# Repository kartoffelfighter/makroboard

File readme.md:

# Makroboard 

This keyboard has 8 cherry switches and 8 rgb-leds, connected to an ATMEGA32U4 (Arduino Leonardo) to emulate a keyboard.

Its porpuse is to store Makros which are not defined per default on a keyboard

## Keys

Default layout (in firmware folder)

| CTRL + F1  | CTRL + F2   | CTRL + F3  | CTRL + F4  |
| ---------- | ----------- | ---------- | ---------- |
| Media_PREV | Media_PAUSE | Media_NEXT | Media_STOP |
|            |             |            |            |
## Dependencies

The firmware uses the FastLed and Project-HID Librarys. You can find these on github, but also in the arduino library manager.

[FastLed (FastLED)]: https://github.com/FastLED/FastLED
[Project-HID (NicoHood)]: https://github.com/NicoHood/HID

### Notes

The Source code is not optimized and might hang sometimes. Since i'm using this board at most to control my teamspeak-mute i didn't care to optimize. If you wan't to, feel free.

Software and Hardware come as-is without any warranty.

My board was etched at jlcpcb, parts came from mouser, assembling was done by hand. 

If you're interested in a board feel free to contact me, i do still have some laying here.

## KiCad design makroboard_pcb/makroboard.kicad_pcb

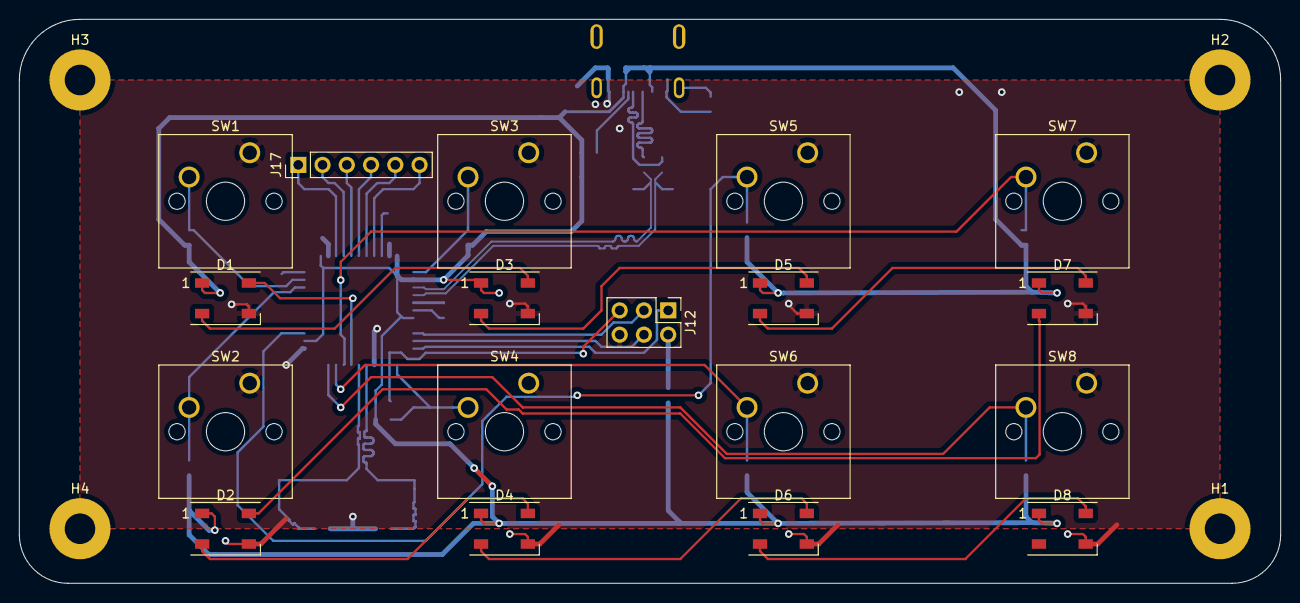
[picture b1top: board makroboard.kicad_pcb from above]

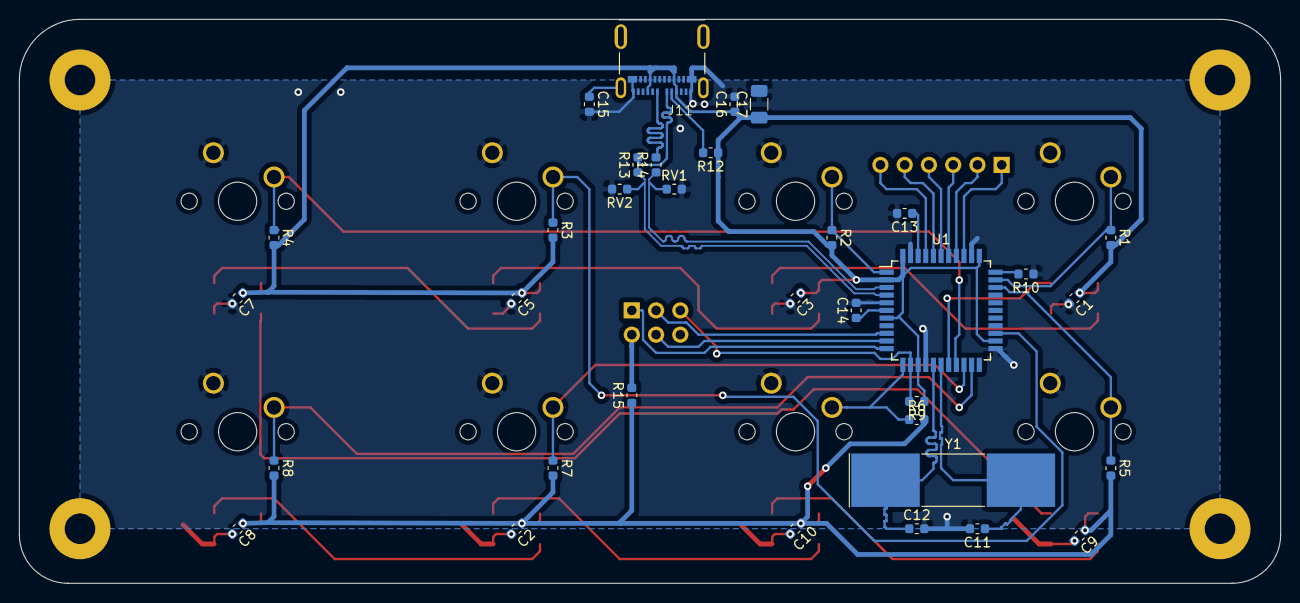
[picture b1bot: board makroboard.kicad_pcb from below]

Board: 2 copper layers, 132.1 x 59.1 mm, 56 parts (34 on the bottom side), 40 nets.

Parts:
C1, C2, C3, C5, C7, C8, C9, C10, C13: 100n; C_0603_1608Metric
C11, C12: 22pF; C_0603_1608Metric
C14: 1µ; C_0603_1608Metric
C15: 1nF; C_0603_1608Metric
C16: 100nF; C_0603_1608Metric
C17: 1µF; C_1206_3216Metric
D1, D2, D3, D4, D5, D6, D7, D8: WS2812B; LED_WS2812B_PLCC4_5.0x5.0mm_P3.2mm
H1, H2, H3, H4: MountingHole_Pad; MountingHole_3.2mm_M3_Pad
J11: 105450-0101; MOLEX_105450-0101
J12: ICSP; PinHeader_2x03_P2.54mm_Vertical
J17: ANALOG_IO; PinHeader_1x06_P2.54mm_Vertical
R1, R2, R3, R4, R5, R6, R7, R8, R9, R10: 10k; R_0603_1608Metric
R12: 56k; R_0603_1608Metric
R13, R14: 22R; R_0603_1608Metric
R15: 0R0; R_0603_1608Metric
RV1, RV2: Varistor; R_0603_1608Metric
SW1, SW2, SW3, SW4, SW5, SW6, SW7, SW8: SW_Push; SW_Cherry_MX_1.50u_PCB
U1: ATmega32U4-AU; TQFP-44_10x10mm_P0.8mm
Y1: 16MHz; Crystal_SMD_SeikoEpson_MA505-2Pin_12.7x5.1mm_HandSoldering

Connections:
+5V: C1.1, C2.1, C3.1, C5.1, C7.1, C8.1, C9.1, C10.1, C16.1, C17.1, D1.1, D2.1, D3.1, D4.1, D5.1, D6.1, D7.1, D8.1, J11.A4, J11.A9, J11.B4, J11.B9, R1.2, R2.2, R3.2, R4.2, R5.2, R6.2, R7.2, R8.2, R9.1, R12.1, R15.1, U1.2, U1.7, U1.14, U1.24, U1.34, U1.44
A0: J17.1, U1.36
A1: J17.2, U1.37
A2: J17.3, U1.38
A3: J17.4, U1.39
A4: J17.5, U1.40
A5: J17.6, U1.41
D0: R7.1, SW6.2, U1.20
D1: R8.1, SW8.2, U1.21
D2: R4.1, SW7.2, U1.19
D3: D1.4, U1.18
D4: R3.1, SW5.2, U1.25
D5: R5.1, SW2.2, U1.31
D7: R2.1, SW3.2, U1.1
D11: R6.1, SW4.2, U1.12
D13: R1.1, SW1.2, U1.32
GND: C1.2, C2.2, C3.2, C5.2, C7.2, C8.2, C9.2, C10.2, C11.2, C12.2, C13.2, C14.2, C15.2, C16.2, C17.2, D1.3, D2.3, D3.3, D4.3, D5.3, D6.3, D7.3, D8.3, J11.A1, J11.A12, J11.B1, J11.B12, J12.6, R10.1, RV1.2, RV2.2, SW1.1, SW2.1, SW3.1, SW4.1, SW5.1, SW6.1, SW7.1, SW8.1, U1.5, U1.15, U1.23, U1.35, U1.43
MISO: J12.1, U1.11
MOSI: J12.4, U1.10
unnamed: C11.1, U1.17, Y1.2
unnamed: C12.1, U1.16, Y1.1
unnamed: C13.1, U1.42
unnamed: C14.1, U1.6
unnamed: C15.1, J11.S1, J11.S2, J11.S3, J11.S4
unnamed: D1.2, D3.4
unnamed: D2.2, D4.4
unnamed: D2.4, D7.2
unnamed: D3.2, D5.4
unnamed: D4.2, D6.4
unnamed: D5.2, D7.4
unnamed: D6.2, D8.4
unnamed: J11.A5, R12.2
unnamed: J11.A6, R13.2
unnamed: J11.A7, R14.2
unnamed: J12.2, R15.2
unnamed: R10.2, U1.33
RESET: J12.5, R9.2, U1.13
SCK: J12.3, U1.9
USB_D+: R13.1, RV2.1, U1.4
USB_D-: R14.1, RV1.1, U1.3

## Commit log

2020-05-24 add: stls for case & current bom
2020-08-16 LICENSE hinzufügen
2020-12-26 working firmware with 8 hotkeys
2020-12-27 add blocking animations for media keys
2020-12-27 added readme
